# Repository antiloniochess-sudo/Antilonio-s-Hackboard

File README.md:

This Is My First Project Ever! I Have Made A HackBoard From A Awseome Tutorial at HackClubs Website.
And sorry if i didn't do every step right, as i said i am completly new to this and could have missed or done something wrong with the case or the submission.

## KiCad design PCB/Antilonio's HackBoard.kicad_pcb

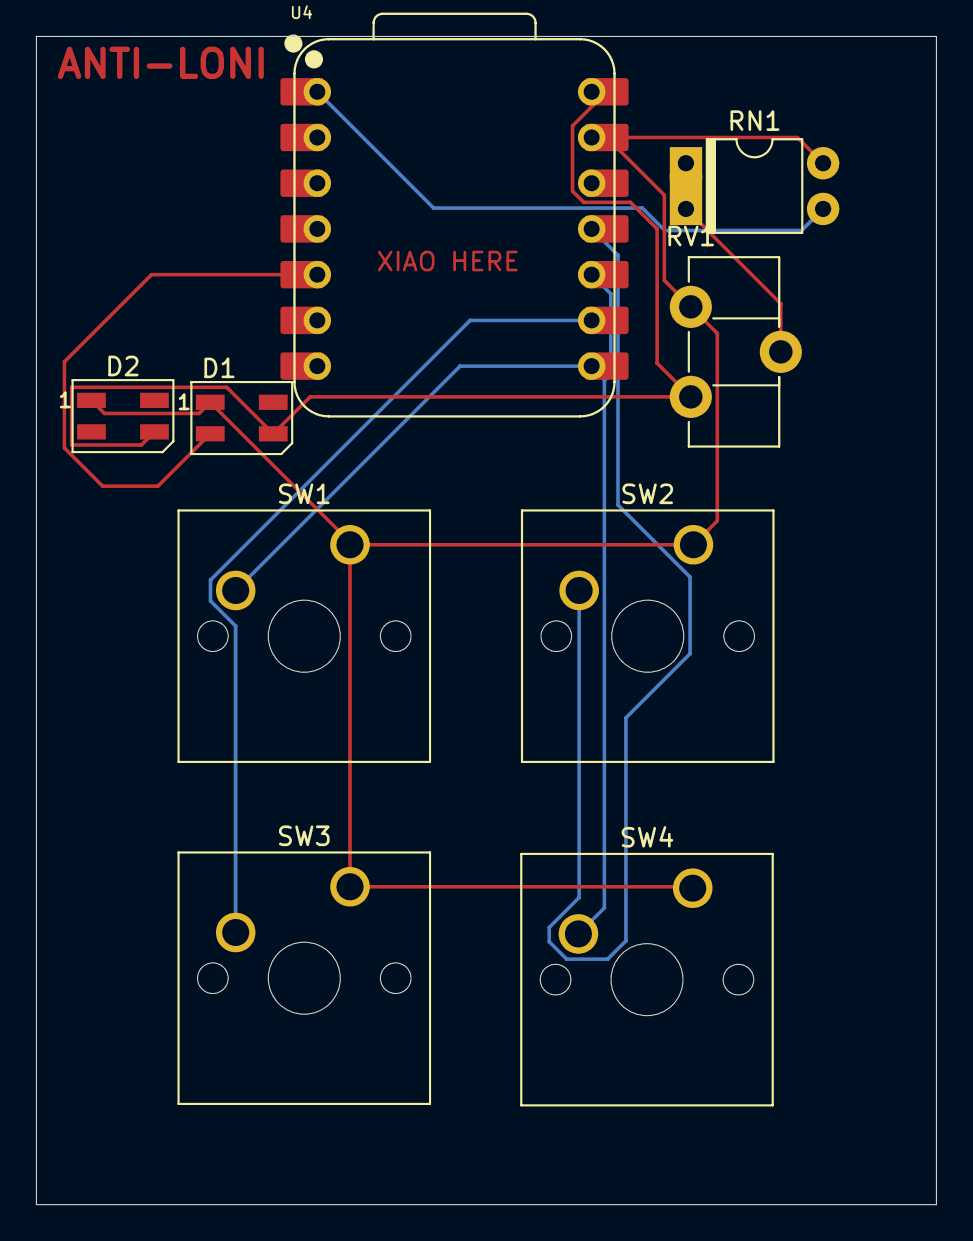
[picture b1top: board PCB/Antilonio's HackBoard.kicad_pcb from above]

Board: 2 copper layers, 50.0 x 64.9 mm, 9 parts (0 on the bottom side), 9 nets.

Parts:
D1, D2: SK6812; LED_SK6812MINI_PLCC4_3.5x3.5mm_P1.75mm
RN1: VoltageDivider; Vishay_HVM-DIP-3_W7.62mm
RV1: R_Potentiometer; Potentiometer_Piher_PT-10-H05_Horizontal
SW1, SW2, SW3, SW4: SW_Push; SW_Cherry_MX_1.00u_PCB
U4: XIAO-RP2040-DIP

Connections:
+5V: D1.3 (VDD), D2.3 (VDD), RV1.3, U4.14 (VBUS)
GND: D1.1 (VSS), D2.1 (VSS), RN1.3, RV1.1, SW1.1, SW2.1, SW3.1, SW4.1, U4.13 (GND)
unnamed: D1.2 (DIN), U4.5 (GPIO6/SDA)
unnamed: RN1.1, RV1.2
unnamed: SW1.2, U4.8 (GPIO1/RX)
unnamed: SW3.2, U4.9 (GPIO2/SCK)
unnamed: SW2.2, U4.11 (GPIO3/MOSI)
unnamed: SW4.2, U4.10 (GPIO4/MISO)
unnamed: RN1.2, U4.1 (GPIO26/ADC0/A0)

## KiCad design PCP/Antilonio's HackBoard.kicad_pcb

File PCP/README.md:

I didnt quite understand the instructions when it said to add the PCB as a blank rectangle. So here is what i thought you meant.
I also added the thing i made in kicad. I meant to write PCB instead i accidentaly wrote PCP.

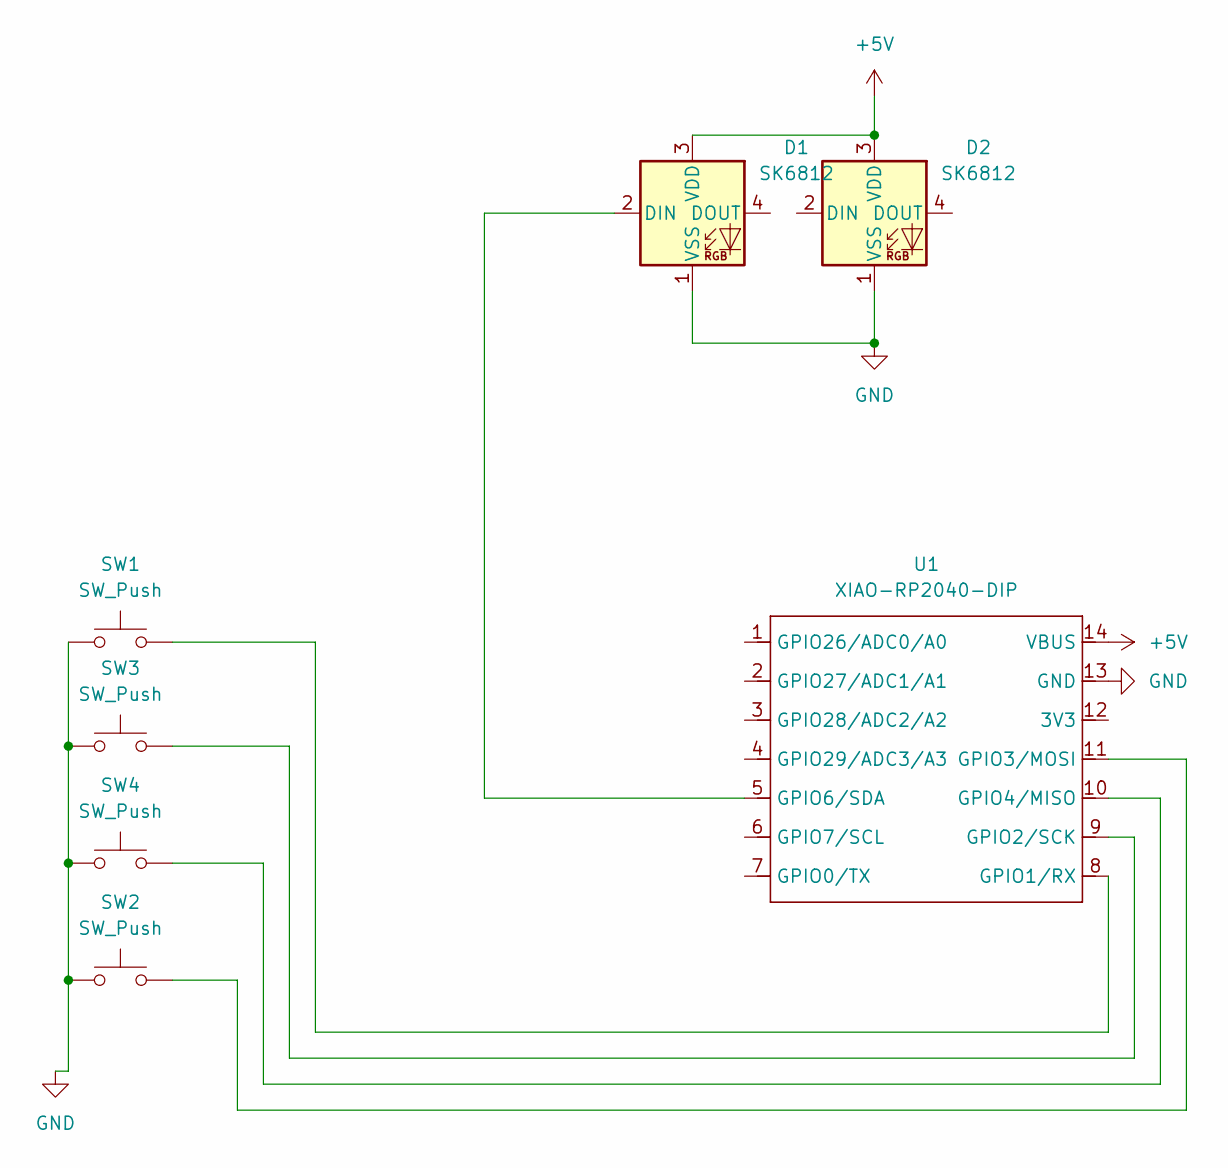
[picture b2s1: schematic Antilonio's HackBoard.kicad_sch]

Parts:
D1, D2: SK6812; LED_SK6812MINI_PLCC4_3.5x3.5mm_P1.75mm
SW1, SW2, SW3, SW4: SW_Push; SW_Cherry_MX_1.00u_PCB
U1: XIAO-RP2040-DIP

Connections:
+5V: D1.3 (VDD), D2.3 (VDD), U1.14 (VBUS)
GND: D1.1 (VSS), D2.1 (VSS), SW1.1, SW2.1, SW3.1, SW4.1, U1.13 (GND)
unnamed: D1.2 (DIN), U1.5 (GPIO6/SDA)
unnamed: SW1.2, U1.8 (GPIO1/RX)
unnamed: SW3.2, U1.9 (GPIO2/SCK)
unnamed: SW2.2, U1.11 (GPIO3/MOSI)
unnamed: SW4.2, U1.10 (GPIO4/MISO)

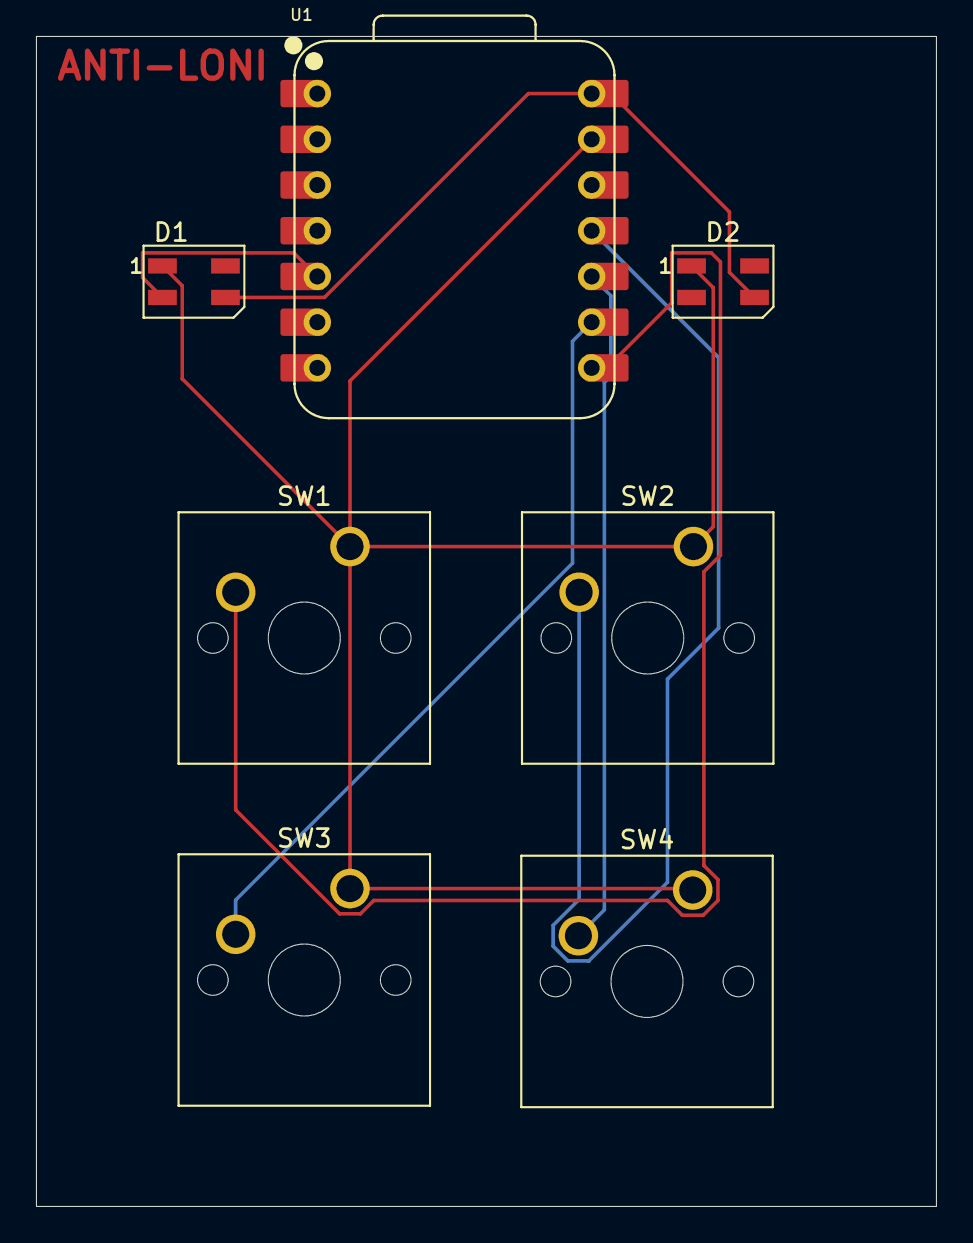
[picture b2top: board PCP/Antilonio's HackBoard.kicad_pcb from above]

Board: 2 copper layers, 50.0 x 65.0 mm, 7 parts (0 on the bottom side), 7 nets.

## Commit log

2026-01-14 Add files via upload
    My Top And Bottom. Seperated
2026-01-14 Add initial project description to README
2026-01-14 Hackboard
2026-01-14 README.md
2026-01-14 Clarify instructions regarding PCB representation
2026-01-14 Create a
2026-01-14 Initialize KMK keyboard firmware in main.py
2026-01-14 README
    Add a personal note about being new to the project.
2026-01-15 Create s
2026-01-15 PCB (I think)
    Clarified misunderstanding of PCB instructions and added KiCad design.
2026-01-15 PCB
    Corrected a typo from 'PCP' to 'PCB' in the README.
2026-01-15 README.me
